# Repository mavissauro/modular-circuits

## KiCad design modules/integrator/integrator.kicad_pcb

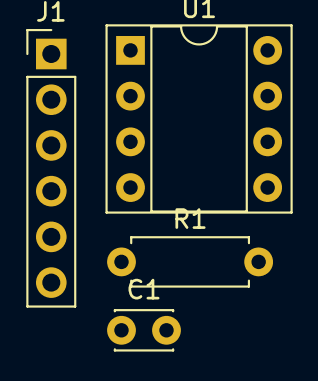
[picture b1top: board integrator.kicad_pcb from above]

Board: 2 copper layers, 4 parts (0 on the bottom side), 5 nets, no tracks yet.

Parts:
C1: C; C_Disc_D3.0mm_W2.0mm_P2.50mm
J1: Conn_01x06_Pin; PinHeader_1x06_P2.54mm_Vertical
R1: R; R_Axial_DIN0207_L6.3mm_D2.5mm_P7.62mm_Horizontal
U1: TL071; DIP-8_W7.62mm_Socket

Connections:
GND: J1.3, U1.3 (+)
unnamed: C1.2, R1.1, U1.2 (-)
module +VCC: J1.1, U1.7 (V+)
module In 1: J1.4, J1.5, R1.2
module Out: C1.1, J1.6, U1.6

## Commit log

2023-08-03 Add ltspice
2023-08-03 Add inversor Integrator
2023-08-03 Add Differentiator
2023-09-06 Add missing circuits
2023-09-16 Add NE555Circuits
2023-09-19 Add Schematic
2023-09-23 Update kicad project
2023-09-24 split modules into individual projects
2023-09-26 Add mainboard schematic
2023-09-29 Add pdf for each module and mainboard
2023-09-30 Update moudules
2023-10-07 Little changes on each schematic
